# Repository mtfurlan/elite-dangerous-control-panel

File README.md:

# RP2040 TinyUSB HID elite dangerous controller
A control panel for Elite Dangerous.

It takes input from the game's
[Status.json](https://elite-journal.readthedocs.io/en/latest/Status%20File.html)
and sends it over HID to the control panel.

That way we can have switches that act like buttons, as well as LEDs.

## HID notes
I had some Issues getting tinyusb working, I tried adafruit's port under platformio and too many things there were annoying and broken.
So eventaully I just ended up using the rp2040 pico-sdk and tinyusb directly.

`.lvimrc` to configure [`vim-ale`](https://github.com/dense-analysis/ale) cause it can't fully get stuff from `compile_commands.json` [yet](https://github.com/dense-analysis/ale/issues/3328)

### USB HID
* [Introduction to HID report descriptors](https://docs.kernel.org/hid/hidintro.html)
* spec
  * [HID 1.11 spec](https://www.usb.org/sites/default/files/hid1_11.pdf)
  * [HID Usage Tables](https://usb.org/sites/default/files/hut1_6.pdf): has usage pages and usage tags and other stuff

* input: data from device -> host like keyboard or joystick
* output: data from host -> device, like keyboard LEDs
* feature report: other stuff
  > "Feature"s are not meant to be consumed by the end user and define configuration options for the device.

#### linux support of HID
Unfortunately, linux doesn't support stuff like weird simulation buttons, so
the only real options are gamepad buttons or keyboard buttons.

[Look at how little of sim is covered](https://github.com/torvalds/linux/blob/master/drivers/hid/hid-input.c#L797-L806).

#### decoding descriptor reports
* [hidrdd](https://github.com/abend0c1/hidrdd)
  * `alias hidrdd="rexx ~/src/hidrdd/rd.rex -i ~/src/hidrdd/rd.conf --no-struct"`
  * `hidrdd -bf /sys/bus/hid/devices/0003\:CAFE\:4003.0060/report_descriptor`
* [online USB Descriptor and Request Parser](http://eleccelerator.com/usbdescreqparser/)
  * `xxd -p /sys/bus/hid/devices/0003\:CAFE\:4003.0060/report_descriptor | tr -d '\n' | copyToClipboard`

#### host side hid tools
```
hidapitester --vidpid CAFE:4003 --open --length 3 --send-output 1,0x00,0x0
```

python [hid](https://pypi.org/project/hid/) wraps [libusb hidapi](https://libusb.info/hidapi/group__API.html)
```
import hid
with hid.Device(vid, pid) as h:
    h.write(bytes([0x01, 0x42, 0, 0, 0]))
```

udev:
```
SUBSYSTEMS=="usb", ATTRS{idVendor}=="cafe", MODE:="0666"
```

### Fun facts about windows
windows will just disregard hid devices with vendor pages without usage min/max, even though it's a vendor page

In actual windows, you can see a (misspelled) error in the device manager.

In wine, I'm not sure how to get any error message.

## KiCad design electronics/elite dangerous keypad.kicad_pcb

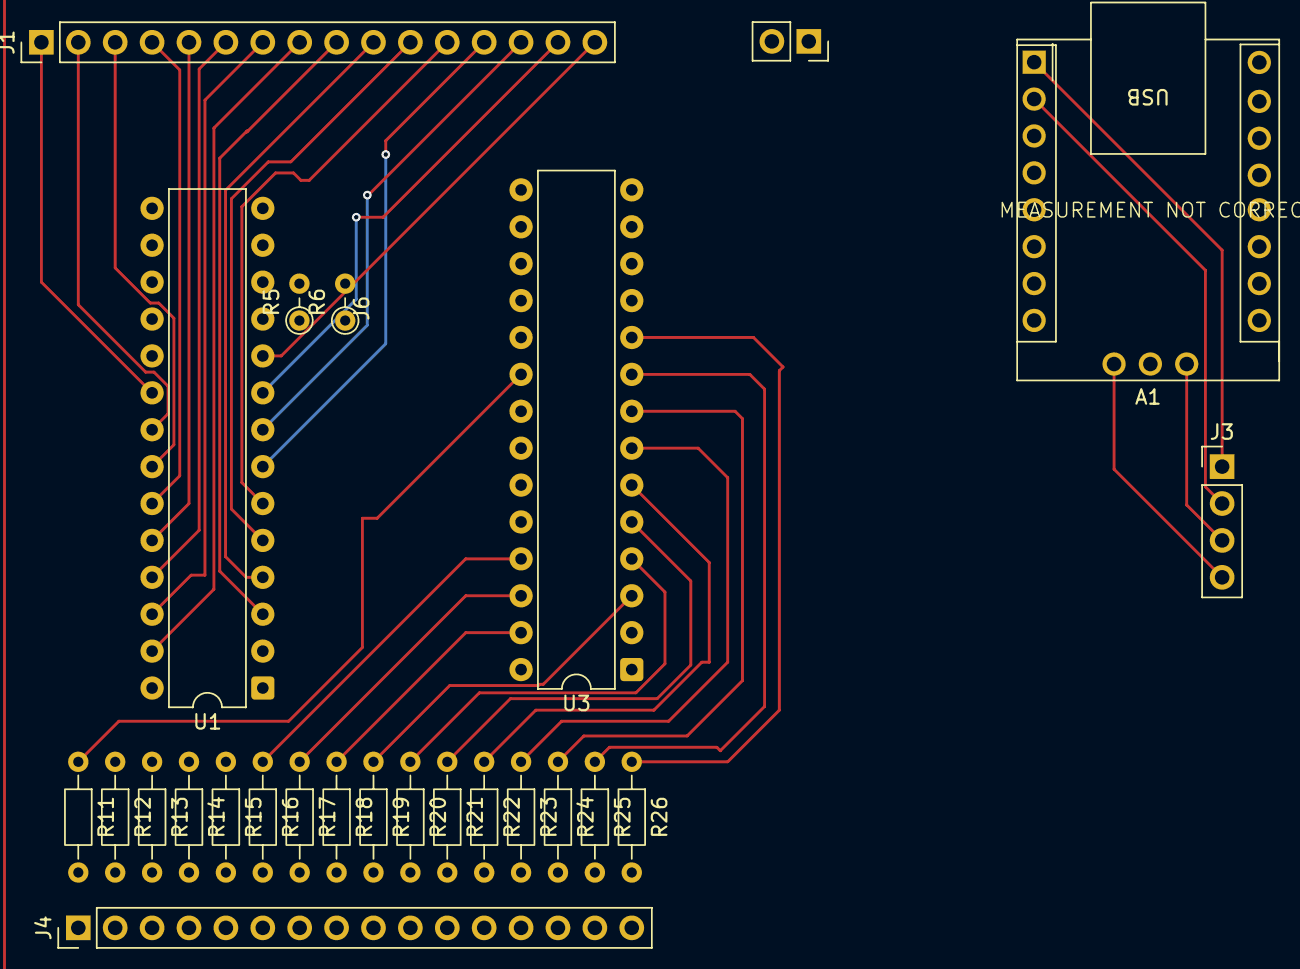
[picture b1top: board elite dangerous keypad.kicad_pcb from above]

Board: 2 copper layers, 25 parts (0 on the bottom side), 55 nets.

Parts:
A1: Tiny2040; Arduino_Nano
J1: button; PinHeader_1x16_P2.54mm_Vertical
J3: swd debug; PinHeader_1x04_P2.54mm_Vertical
J4: led; PinHeader_1x16_P2.54mm_Vertical
J6: Conn_01x02; PinSocket_1x02_P2.54mm_Vertical
R5, R6: 1k5; R_Axial_DIN0204_L3.6mm_D1.6mm_P2.54mm_Vertical
R11, R12, R13, R14, R15, R16, R17, R18, R19, R20, R21, R22, R23, R24, R25, R26: R; R_Axial_DIN0204_L3.6mm_D1.6mm_P7.62mm_Horizontal
U1, U3: MCP23018x-x-SP; DIP-28_W7.62mm

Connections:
+5V: A1.1 (5V), J3.1, J6.1, R5.1, R6.1, U1.11 (V_{DD}), U1.16 (~RESET), U3.11 (V_{DD}), U3.15 (ADDR), U3.16 (~RESET)
/B0: J1.1, U1.20 (GPA0)
/B1: J1.2, U1.21 (GPA1)
/B2: J1.3, U1.22 (GPA2)
/B3: J1.4, U1.23 (GPA3)
/B4: J1.5, U1.24 (GPA4)
/B5: J1.6, U1.25 (GPA5)
/B6: J1.7, U1.26 (GPA6)
/B7: J1.8, U1.27 (GPA7)
/B8: J1.9, U1.3 (GPB0)
/B9: J1.10, U1.4 (GPB1)
/B10: J1.11, U1.5 (GPB2)
/B11: J1.12, U1.6 (GPB3)
/B12: J1.13, U1.7 (GPB4)
/B13: J1.14, U1.8 (GPB5)
/B14: J1.15, U1.9 (GPB6)
/B15: J1.16, U1.10 (GPB7)
/L0: R11.1, U3.20 (GPA0)
/L1: R12.1, U3.21 (GPA1)
/L2: R13.1, U3.22 (GPA2)
/L3: R14.1, U3.23 (GPA3)
/L4: R15.1, U3.24 (GPA4)
/L5: R16.1, U3.25 (GPA5)
/L6: R17.1, U3.26 (GPA6)
/L7: R18.1, U3.27 (GPA7)
/L8: R19.1, U3.3 (GPB0)
/L9: R20.1, U3.4 (GPB1)
/L10: R21.1, U3.5 (GPB2)
/L11: R22.1, U3.6 (GPB3)
/L12: R23.1, U3.7 (GPB4)
/L13: R24.1, U3.8 (GPB5)
/L14: R25.1, U3.9 (GPB6)
/L15: R26.1, U3.10 (GPB7)
/MCU_INPUT_INT: A1.10 (6), U1.19 (INTA)
/SCL: A1.11 (5), R5.2, U1.12 (SCL), U3.12 (SCL)
/SDA: A1.12 (4), R6.2, U1.13 (SDA), U3.13 (SDA)
GND: A1.2 (GND), J3.2, J6.2, U1.1 (V_{SS}), U1.15 (ADDR), U3.1 (V_{SS})
unnamed: A1.SWD, J3.3
unnamed: A1.SWC, J3.4
unnamed: J4.1, R11.2
unnamed: J4.2, R12.2
unnamed: J4.3, R13.2
unnamed: J4.4, R14.2
unnamed: J4.5, R15.2
unnamed: J4.6, R16.2
unnamed: J4.7, R17.2
unnamed: J4.8, R18.2
unnamed: J4.9, R19.2
unnamed: J4.10, R20.2
unnamed: J4.11, R21.2
unnamed: J4.12, R22.2
unnamed: J4.13, R23.2
unnamed: J4.14, R24.2
unnamed: J4.15, R25.2
unnamed: J4.16, R26.2

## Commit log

2025-10-23 pico-sdk hid_composite example with debugging
2025-10-23 try to do cdc and hid, doesn't work
2025-10-23 modified usb cdc example doesn'tw ork
2025-10-23 working
2025-10-23 button works
2025-10-23 better gdb config
2025-10-23 only gamepad and keyboard now
2025-10-23 only send a gamepad button event; gdbconfig reset better
2025-10-27 description and messing with hid
2025-10-27 partial config stuff
2025-10-27 switch stuff; input stuff works
2025-10-28 buttons and leds work but wine doesn't now?
2025-10-28 works fully; windows cannot handle spaceship sim
2025-10-29 s/main.c/main.cpp/
    also rename hidReport to hid
2025-10-29 add mcp lib deps
2025-10-29 s/c/cpp/
2025-10-29 feat: buttons use mcp
2025-10-30 led mcp works
2025-10-30 use uint16_t for data, not doing four MCPs right now
2025-10-30 config map works for direct
2025-10-30 refactor(config struct): field names
2025-10-30 add kicad schematic
2025-10-30 feat: error on init error
2025-10-30 partial SMART thoughts
2025-10-30 refactor: lint with clang-format
2025-10-30 smart button works, but apparently I'm not writing hid buttons properly
    they all show up as button 1
2025-10-30 ci: linter bug
2025-10-30 fix(hid reporting): report data, fix hid desc report
2025-10-30 smart button works!
2025-10-31 feat: send all Status.json data
2025-10-31 refactor: struct names
2025-10-31 refactor(usb_descriptors.c): naming & cleanup
2025-11-03 feat: picotool reset (needs sdk PR 2629)
2025-11-03 feat: button config better ish
2025-11-03 schematic for cardboard box version
2025-11-03 docs(README): is ed not generic, better words
2025-11-03 feat: Makefile
2025-11-03 debug and flash script args
2025-11-03 fix(sendData): name typo, debug bad json
2025-11-08 fix(hid): last button works again
    skipped button 13 wrong
2025-11-08 fix(sendData): handle broken json from game
2025-11-12 feat(buttons): add buttons_read function
2025-11-12 fix(config): 1 index button/led pins for consistancy
2025-11-15 refactor: use cpp classes for input config
    instead of struct array and switches to handle a mode enum, use classes
2025-11-15 refactor(classes): split up led and button better
    now we have the config base class, an led class, and a button class
    smart switch takes led and button and extends the deciding part
2025-11-15 refactor: VButton class to handle virtual buttons
    ConfigSmart is *so much* simpler and everything is easier to read now
2025-11-15 refactor: config btn track last state, vbutton better
2025-11-16 feat(quadrature): use quad encoders as buttons
    cpp types are weird
2025-11-16 chore: git diff exclude kicad files
2025-11-16 feat(electronics): quadrature schematic
2025-11-17 refactor(config): s/checkConfig/init/
2025-11-17 docs(electronics): label KY-040 resistors
2025-12-10 docs(electronics): reformat for readability
2025-12-10 fix(smart btn): increase timeout
    with the edmc plugin it's a bit slower, so we need more timeout
2025-12-10 chore(sendData): capitalization
2025-12-10 quadrature debugging
2026-03-03 docs: note that I'm using a PR for usb reset
2026-03-03 note that I'm using a PR for usb reset
2026-04-21 build: pico sdk as submodule; tools dir
2026-04-21 build: include QuadratureDecoder
2026-04-21 remove all button handling in prep for rewrite
2026-04-22 stuff
2026-04-22 works ish
2026-04-22 encoder
2026-04-22 comment mcp stuff
2026-04-27 button start
2026-04-27 cleanup
